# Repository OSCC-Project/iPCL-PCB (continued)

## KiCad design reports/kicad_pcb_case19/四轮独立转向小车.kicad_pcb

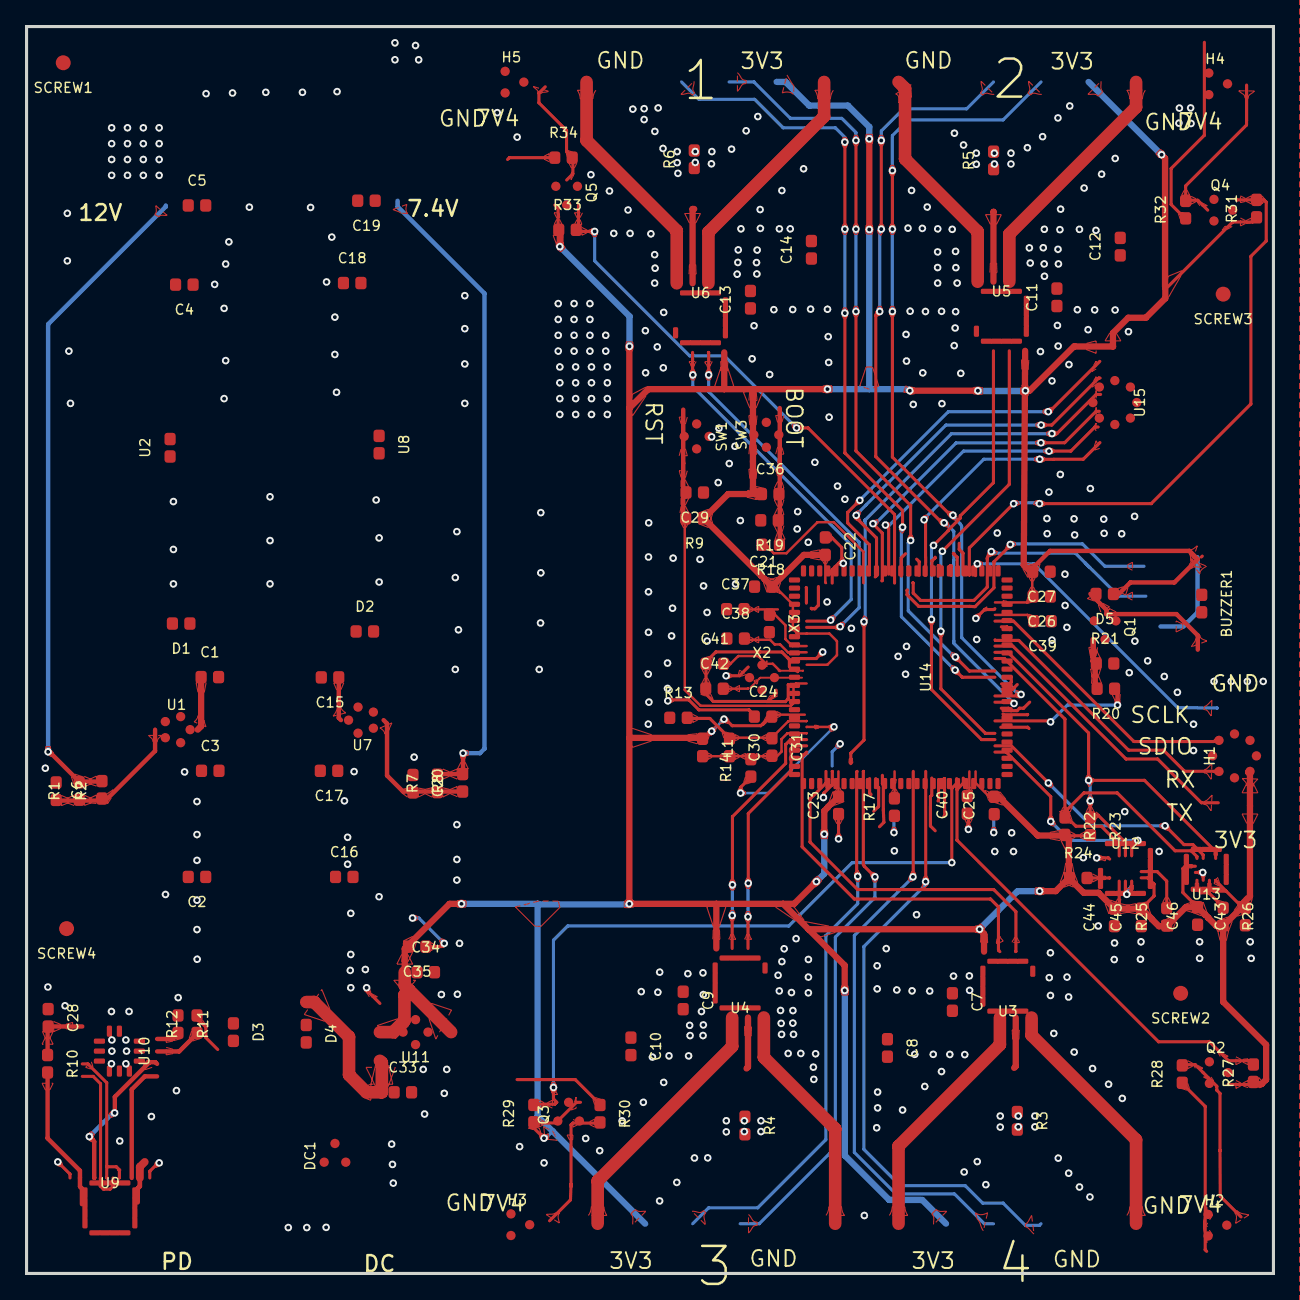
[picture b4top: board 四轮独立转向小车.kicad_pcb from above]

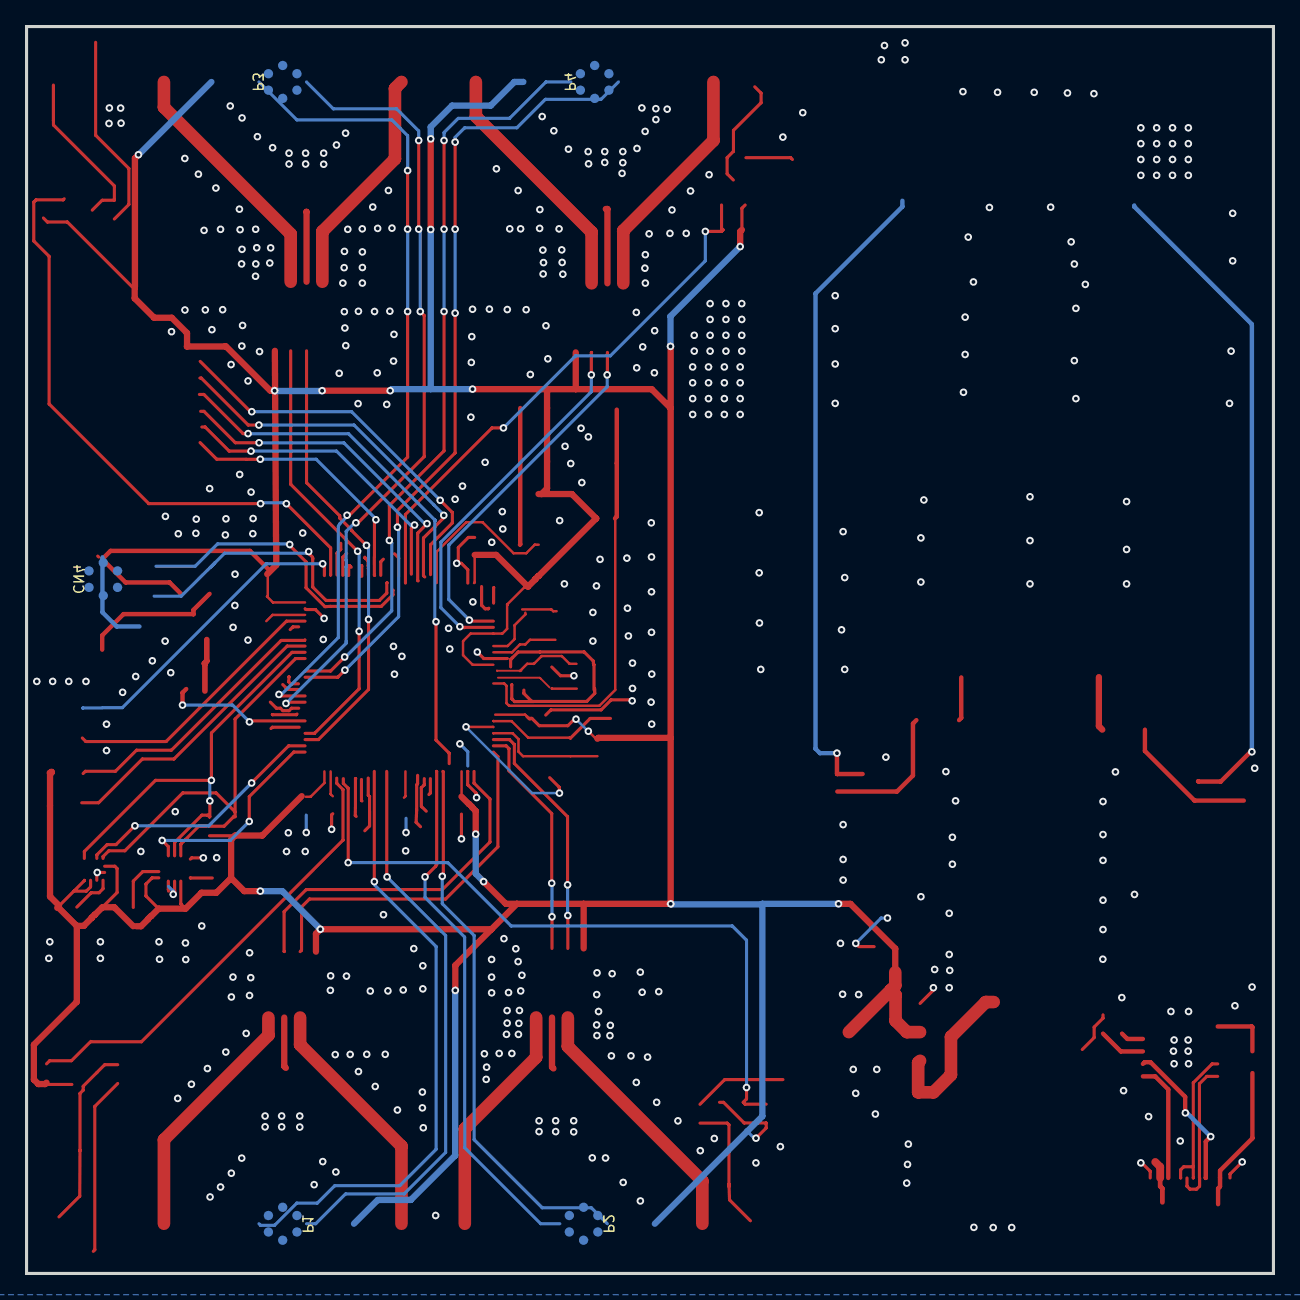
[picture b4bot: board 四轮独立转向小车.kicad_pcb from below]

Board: 4 copper layers, 100.0 x 100.0 mm, 123 parts (5 on the bottom side), 91 nets.

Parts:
BUZZER1: e979cdb000ab4426b6223529a4e12ad8
C1, C3, C4, C6, C7, C9, C11, C13, C15, C17, C18, C20, C21, C22, C23, C24, C25, C26, C27, C28, C29, C30, C31, C35, C36, C37, C38, C41, C42, C43, C44, C45, C46: 741784fa20ad4beab9dd8b8cbce97607
C2, C16: 64fdc954f1a842c2a61e7a3a428ba0e8
C5, C19: aa257ccdfc444fe68fbfe26cfeed8af2
C8, C10, C12, C14: 5d8616532ae7487fa34b3cfaab35ec0e
C33, C34: aff1c91bf3bd4904ada184bcb63bd701
C39, C40: ca2c3d94d51b4dcc8ffcb1d0c67fae6c
CN4: a37b095bfeb148db8b87bdfda393230c
D1, D2, D3, D4: ada4b0e957a340438272a068e350ca08
D5: 7c72a01ebf81492eadadbaccff803c14
DC1: a60ba02c803547268dd5888f05c1003b
H1: 648849d55ce94beca6d893b0b88daeda
H2, H3, H4, H5: abe8049b303d404e805f87de02117873
L1: 5148ca10eaa2479eac7b76f1cbba51f9
P1, P2, P3, P4: 0d6f8f50dd17470faea1144c4daec37b
Q1, Q2, Q3, Q4, Q5: d368db2ef12b40499e45a74d16a73474
R1, R2, R7, R8, R9, R11, R12, R13, R14, R17, R18, R19, R21, R22, R23, R24, R25, R26, R27, R28, R29, R30, R31, R32, R33, R34: 1996b2fb973e40a184d52a2e5e193df3
R3, R4, R5, R6: 24935121d17843519fd4a5b349af625d
R10: 4344cacefc0949e29a8e228f16c4cb32
R20: 446156e8ca504404ab86e8dd60b77f34
SCREW1: e53
SCREW2: e54
SCREW3: e55
SCREW4: e56
SW1, SW3: f78937a3961e46c7aa83ae3777a1ced1
U1, U7: 0156e8566a5e4bc490068a3a1a138cdb
U2, U8: a6e5a65120164f159c520d6f95081e2c
U3, U4, U5, U6: 306ac8a366164cb2a66e359fb6504e2e
U9: df7c89edaee04039b94d8ad6f54aed48
U10: 6103e188eda54d98b9a4d66887e412bf
U11: eb6f0a55a64841b28a24ff6840c76e95
U12: 9212da6725b641f1870fb3cf18556f1c
U13: a1272321b06a4e088013c99c4785c5c8
U14: ac645093d34d4da5947e929ac4406eff
U15: 91d99640c4a348eb8a20141652c3be94
X2: 028e88c81bcf4cf5a4c76024a7a6c317
X3: 518fd2fe129c4e2f80eda365652bfc47

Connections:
7.4V: C18.2, C19.1, C20.2, H2.2, H3.2, H4.2, H5.2, R7.2, R28.1, R30.1, R32.1, R34.1, U8.2
12V: C4.2, C5.1, C6.2, C7.2, C8.1, C9.2, C10.1, C11.2, C12.1, C13.2, C14.1, R1.2, U2.2, U3.5, U4.5, U5.5, U6.5
$1N946: P1.1, U3.8
$1N950: P1.6, U3.6
$1N1291: R3.1, U3.7
$1N2982: C1.1, U1.4
$1N3021: D1.1, U1.3, U2.1
$1N3970: C6.1, R1.1, R2.2, U1.2
$1N4759: P2.6, U4.6
$1N4761: R4.1, U4.7
$1N4762: P2.1, U4.8
$1N5052: P3.6, U5.6
$1N5054: R5.1, U5.7
$1N5055: P3.1, U5.8
$1N5345: P4.6, U6.6
$1N5347: R6.1, U6.7
$1N5348: P4.1, U6.8
$1N5797: C20.1, R7.1, R8.2, U7.2
$1N5800: D2.1, U7.3, U8.1
$1N5801: C15.1, U7.4
$1N15768: H2.3, Q2.3, R28.2
$1N16087: H3.3, Q3.3, R30.2
$1N16294: H4.3, Q4.3, R32.2
$1N16459: H5.3, Q5.3, R34.2
$2N2977: C40.2, U14.49
$2N2980: C39.2, U14.73
$2N2999: R14.1, U14.21
$2N3034: C36.2, R18.1, R19.1, SW3.3, SW3.4
$2N5724: R17.2, U14.37
$2N6021: U9.A6, U9.B6, U10.4
$2N6027: U9.A7, U9.B7, U10.5
$2N6224: R12.1, U10.8
$2N6576: R11.2, U10.9
$2N6889: D4.3, DC1.1
$2N8508: R24.2, U12.4
$2N8534: R25.2, U12.9
$2N8540: R26.1, U13.7
$2N11019: BUZZER1.2, D5.2, Q1.3
$2N11066: Q1.1, R20.2, R21.1
+3V3: BUZZER1.1, C21.2, C22.2, C23.2, C24.2, C25.2, C26.2, C27.2, C34.1, C35.2, C36.1, C43.2, C44.2, C45.2, C46.2, CN4.4, D5.1, H1.1, H1.3, L1.1, P1.5, P2.5, P3.5, P4.5, Q2.1, Q3.1, Q4.1, Q5.1, R9.1, R22.2, R23.2, R24.1, R25.1, R26.2, R27.1, R29.1, R31.1, R33.1, SW3.1, SW3.2, U3.4, U4.4, U5.4, U6.4, U11.2, U11.4, U12.5, U12.8, U13.5, U13.9, U13.10, U14.6, U14.11, U14.19, U14.28, U14.50, U14.75, U14.100, U15.1
AGND: C30.1, C31.1, R13.2, U14.20
B1A: P4.3, U14.63
B1B: P4.4, U14.64
B2A: P3.3, U14.59
B2B: P3.4, U14.60
B3A: P2.3, U14.32
B3B: P2.4, U14.31
B4A: P1.3, U14.42
B4B: P1.4, U14.40
BOOT0: R18.2, U14.94
BUZZ: R20.1, U14.56
CC1: U9.A5, U10.7
CC2: U9.B5, U10.6
CE: U14.93, U15.2
CS1: U12.12, U14.51
CS2: U13.3, U14.52
CSN: U14.92, U15.3
GND: C2.2, C3.1, C4.1, C5.2, C7.1, C8.2, C9.1, C10.2, C11.1, C12.2, C13.1, C14.2, C16.2, C17.1, C18.1, C19.2, C21.1, C22.1, C23.1, C24.1, C25.1, C26.1, C27.1, C28.1, C29.1, C33.2, C34.2, C35.1, C37.1, C38.1, C39.1, C40.1, C41.1, C42.1, C43.1, C44.1, C45.1, C46.1, CN4.1, D1.3, D2.3, DC1.2, DC1.3, H1.5, H1.7, H2.1, H3.1, H4.1, H5.1, P1.2, P2.2, P3.2, P4.2, Q1.2, R2.1, R3.2, R4.2, R5.2, R6.2, R8.1, R11.1, R13.1, R17.1, R19.2, R21.2, SW1.1, SW1.2, U1.1, U3.1, U3.9, U3.e36, U3.e37, U3.e38, U3.e39, U4.1, U4.9, U4.e36, U4.e37, U4.e38, U4.e39, U5.1, U5.9, U5.e36, U5.e37, U5.e38, U5.e39, U6.1, U6.9, U6.e36, U6.e37, U6.e38, U6.e39, U7.1, U9.A1B12, U9.B1A12, U10.11, U11.1, U12.1, U12.6, U12.7, U13.6, U13.8, U14.10, U14.27, U14.74, U14.99, U15.8, X2.2, X2.4
IRQ: U14.84, U15.7
MISO: U14.90, U15.6
MOSI: U14.91, U15.5
NRST: C29.2, R9.2, SW1.3, SW1.4, U14.14
OSC32_IN: C37.2, U14.8, X3.1
OSC32_OUT: C38.2, U14.9, X3.2
OSC_IN: C41.2, U14.12, X2.3
OSC_OUT: C42.2, U14.13, X2.1
PWM1A: U6.3, U14.5
PWM1B: U6.2, U14.4
PWM1C: Q5.2, R33.2, U14.89
PWM2A: U5.3, U14.54
PWM2B: U5.2, U14.53
PWM2C: Q4.2, R31.2, U14.77
PWM3A: U4.3, U14.23
PWM3B: U4.2, U14.24
PWM3C: Q3.2, R29.2, U14.47
PWM4A: U3.3, U14.25
PWM4B: U3.2, U14.26
PWM4C: Q2.2, R27.2, U14.48
SCL: R23.1, U12.13, U13.1, U14.67
SDA: R22.1, U12.14, U13.4, U14.66
SPI-SCLK: U14.30, U15.4
SWCLK: H1.8, U14.76
SWDIO: H1.6, U14.72
USART1_RX: H1.4, U14.69
USART1_TX: H1.2, U14.68
USART2_RX: CN4.2, U14.87
USART2_TX: CN4.3, U14.86
VBUS: D3.3, R10.2, R12.2, U9.A4B9, U9.B4A9
VDD: C28.2, R10.1, U10.1
VDDA: C30.2, C31.2, L1.2, R14.2, U14.22
VIN: C1.2, C2.1, C3.2, C15.2, C16.1, C17.2, C33.1, D3.1, D4.1, U1.5, U7.5, U11.3

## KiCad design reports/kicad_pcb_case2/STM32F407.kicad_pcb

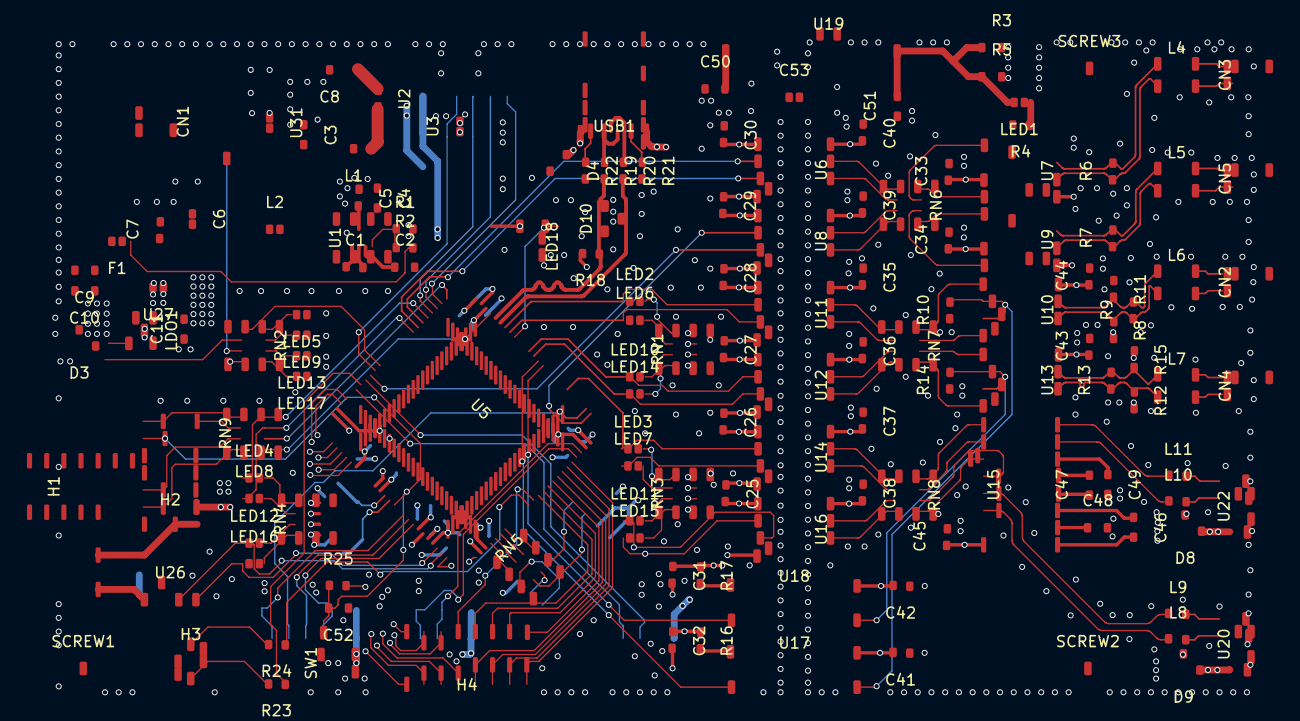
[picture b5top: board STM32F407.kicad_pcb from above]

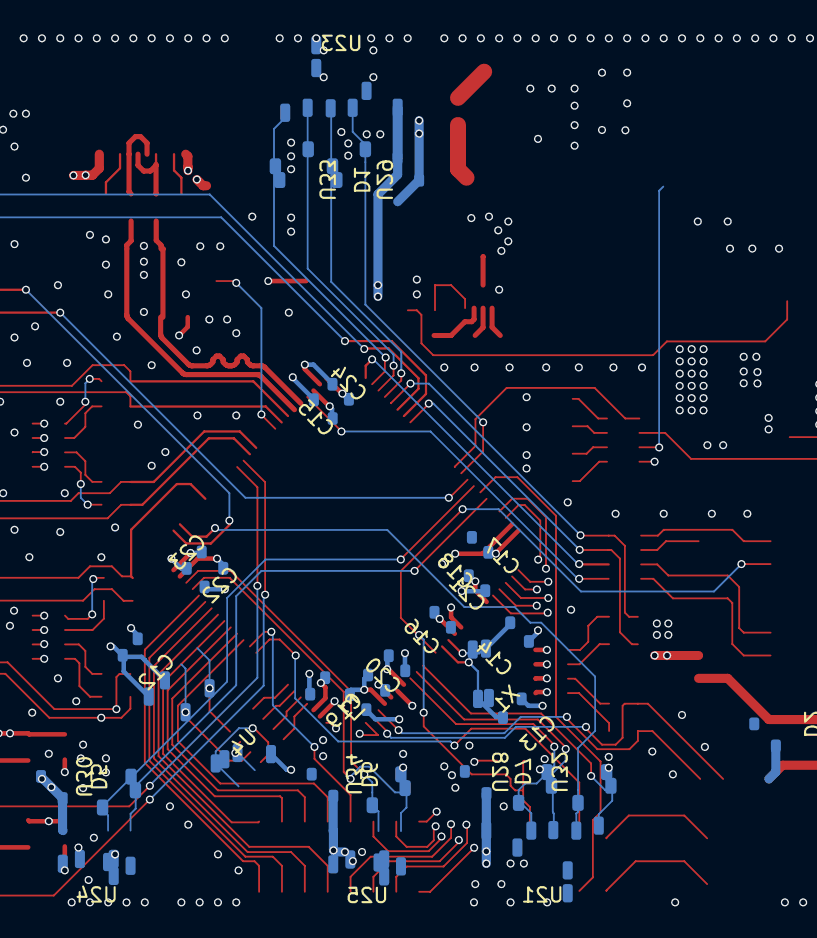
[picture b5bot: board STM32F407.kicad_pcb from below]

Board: 4 copper layers, 177 parts (31 on the bottom side), 166 nets.

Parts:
C1, C5, C7, C12, C15, C16, C17, C18, C19, C20, C21, C22, C25, C26, C27, C28, C29, C30, C31, C32, C33, C34, C35, C36, C37, C38, C39, C40, C41, C42, C43, C44, C45: ebdba0498fe148a6bdaf1849ccadf286
C2, C3, C4, C9, C10, C11, C13, C14, C23, C24, C46, C47, C48, C49, C50, C51, C52: 5c1039116f0d4a48a63c516b3468eedc
C6: 77c1372840904ec4adfa70989b453f34
C8: dac8b4b5750744debf3e22cc36519d09
C53: 722f0fd63bc245dcb5bb6f1de9d44fc4
CN1: a8d795644714433aa9d8ef5899e54b7c
CN2, CN3, CN4, CN5: 8dc8f08645254a7c933896da55491e27
D1, D2, D3, D4, D5, D6, D7, D8, D9: 9031908bb42048fd9eda99e7ea0ed57d
D10: 1d12765dce444169bea8a89c91ace60b
F1: acac5cdf7cf0489f95c57cd956ebba05
H1: c4b2aa7e7e9449449c802d818131b083
H2: c177e7ff2bbf4de4802e46bae8c17754
H3: af64557c0fc140ad852d5d3869016491
H4: 13fd0b7dd5f1483f9419a67b629bdedc
L1: e9d87c9fa1e64efe9140f423ad4aface
L2: 24042ba1875b4ae68b2524adc495f30d
L3, L8, L9, L10, L11: 89a8af1840c5419aa6d14d56da4c8ebb
L4, L5, L6, L7: 2578ce3ca2c0496d87f2ce74849d3ae0
LDO1: 960ec4bb3aa44deea5cfb00bee97f891
LED1: e119
LED2: e121
LED3: e127
LED4: e129
LED5: e114
LED6: e120
LED7: e128
LED8: e137
LED9: e183
LED10: e126
LED11: e180
LED12: e138
LED13: e115
LED14: e122
LED15: e181
LED16: e145
LED17: e182
LED18: 43ac071a49e04e77baa710baadd2d193
R1, R2, R4, R6, R7, R8, R9, R10, R11, R12, R13, R14, R15, R16, R17, R18, R19, R20, R21, R22, R23, R24, R25: 8eb41c1356a64d5a89688063e5a29866
R3, R5: 1b18a010265d471c96efb00eae83c3fd
RN1, RN2, RN3, RN4, RN5, RN6, RN7, RN8, RN9: 2d9df88f5cb64a93977683380616dc51
SCREW1: e123
SCREW2: e124
SCREW3: e125
SW1: efcb0d994e4a4c97aabd31c9830287d5
U1: 15c443d2e1db4dc2b94e34a7db02dd20
U2: 8eb41c1356a64d5a89688063e5a29866
U3: 94e88e65a31343e1b2ef320e804c3fe9
U4: ed3ae879f37841489638cf463064b2e9
U5: 702827d8cd244652a8c957c2584a68a3
U6, U8, U11, U12, U14, U16: 51f0659d1b89481c952678486102db75
U7, U9: 795edbe8080c42678b7c83009ee8dda9
U10, U13: 08b2b6f7ec8347719ef9c282fbdb4a98
U15: f02a3915c41541a1876bc8493e75c0a5
U17, U18: 6089bf52aced4419a38cccb1e1e2119c
U19: 7f6d8a3a13634d468399499959319597
U20, U22, U24, U25: a9433511565944b6b4d3b77f9386d7fd
U21, U23: 48e620de49c44dc5874424a0f0b4b8ec
U26: 6fb28d1a64be4bf99e264b9b66ea87b4
U27: 1bfae8d0649a41a59c4de595a2b109d1
U28, U29, U30, U32, U33, U34: 2d09ce42ff4448d79a78d05c1c820847
U31: 3e6dba7158d148109233be8d25d8f9b1
USB1: 7e44e2b238ab4ac2876cbe0247efab15
X1: 2f487b9613c04c2f98ecb5797db40c7a

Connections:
232_1_RX: L8.2, U20.3
232_1_TX: L9.2, U20.4
232_2_RX: L10.2, U22.3
232_2_TX: L11.2, U22.4
485_1_A: CN2.1, L6.3
485_1_B: CN2.2, L6.4
485_2_A: CN4.1, L7.3
485_2_B: CN4.2, L7.4
$1N123763: C8.1, U2.1
$1N124316: C4.2, C5.2, L1.2, U1.3, U2.2, U3.1
$1N124327: C1.1, L2.1, U1.5
$1N124343: C1.2, U1.6
$1N124356: R1.1, R2.1, U1.8
$1N124450: C2.1, U1.7
$1N125064: LED1.1, R4.1
$1N125152: LED2.2, RN1.5
$1N131581: LED4.2, RN4.5
$1N131583: LED8.2, RN4.6
$1N131585: LED12.2, RN4.7
$1N131593: LED16.2, RN4.8
$1N140993: LED5.2, RN2.8
$1N141105: LED13.2, RN2.6
$1N141109: LED17.2, RN2.5
$1N141153: LED9.2, RN2.7
$1N141345: C6.2, C7.1, F1.1, L2.2, R2.2
$1N145605: LED3.2, RN3.5
$1N145607: LED7.2, RN3.6
$1N145659: LED15.2, RN3.8
$1N145661: LED11.2, RN3.7
$1N145713: LED14.2, RN1.8
$1N145715: LED10.2, RN1.7
$1N145775: LED6.2, RN1.6
$2N590: C23.1, U5.49
$2N591: C24.1, U5.73
$2N663: L3.2, U5.21
$3N1505: H2.7, RN9.6
$3N1506: H2.8, RN9.5
$3N1507: H2.12, RN9.7
$3N1508: H2.13, RN9.8
$3N1509: H3.3, R23.2
$3N1516: H3.4, R24.2
$3N5226: R22.1, USB1.10
$3N5265: R21.1, USB1.4
$3N6048: R19.1, USB1.6, USB1.8
$3N6052: R20.1, USB1.5, USB1.7
$4N2206: L4.1, R6.2, U7.7
$4N6216: RN8.1, U14.7
$4N6221: RN8.3, U16.7
$4N6226: RN8.4, U16.6
$4N6231: RN8.2, U14.6
$4N6248: RN7.2, U11.6
$4N6252: RN7.1, U11.7
$4N6256: RN7.4, U12.6
$4N6260: RN7.3, U12.7
$4N6264: RN6.2, U6.6
$4N6268: RN6.1, U6.7
$4N6272: RN6.4, U8.6
$4N6276: RN6.3, U8.7
$4N8748: RN6.8, U7.4
$4N8754: RN6.7, U7.1
$4N8812: L4.2, R6.1, U7.6
$4N8845: RN6.6, U9.4
$4N8849: RN6.5, U9.1
$4N9061: L5.1, R7.2, U9.7
$4N9079: L5.2, R7.1, U9.6
$4N10322: RN7.7, U10.4
$4N11551: RN7.8, U10.1
$4N11569: RN7.5, U13.4
$4N11573: RN7.6, U13.1
$4N12037: L7.2, R12.1, R13.1, U13.6
$4N12047: L7.1, R13.2, R15.2, U13.7
$4N12057: L6.1, R9.2, R11.2, U10.7
$4N12067: L6.2, R8.1, R9.1, U10.6
$4N28005: C48.1, U15.2
$4N29856: C49.1, U15.6
$4N29863: C46.2, U15.1
$4N29865: C47.1, U15.4
$4N29900: C46.1, U15.3
$4N29905: C47.2, U15.5
$4N29961: RN8.7, U15.10
$4N29965: RN8.8, U15.9
$4N29970: RN8.5, U15.11
$4N29975: RN8.6, U15.12
$4N30026: L8.1, U15.14
$4N30067: L9.1, U15.13
$4N30105: L10.1, U15.7
$4N30146: L11.1, U15.8
$4N30658: R16.2, U17.1
$4N30711: R17.2, U18.1
+5V: C9.1, C10.1, C25.2, C26.2, C27.2, C28.2, C29.2, C30.2, C31.1, C32.1, C50.2, D1.1, D2.1, D3.1, D4.1, D5.1, D6.1, D7.1, F1.2, H1.1, H1.2, H1.3, H1.4, H1.5, H1.6, H1.7, H2.1, LDO1.1, LDO1.3, LED18.1, R16.1, R17.1, RN2.2, U6.1, U8.1, U11.1, U12.1, U14.1, U16.1, U19.1, U21.1, U23.1, U24.1, U25.1, U26.1, USB1.2, USB1.11
+5V_A: C33.1, C34.1, C35.2, C36.2, C37.2, C38.2, C39.2, C40.2, C41.2, C42.2, C43.1, C44.1, C45.1, C51.2, D8.1, D9.1, LED1.2, R3.1, R5.1, R8.2, R12.2, U6.8, U7.3, U7.5, U8.8, U9.3, U9.5, U10.8, U11.8, U12.8, U13.8, U14.8, U15.16, U16.8, U17.4, U18.4, U19.4, U20.1, U22.1
BOOT0: R23.1, U5.94
BOOT1: R24.1, U5.37
CAN_1_H: CN3.2, L4.4
CAN_1_L: CN3.1, L4.3
CAN_1_RX: U5.81, U6.2
CAN_1_TX: U5.82, U6.3
CAN_2_H: CN5.2, L5.4
CAN_2_L: CN5.1, L5.3
CAN_2_RX: U5.51, U8.2
CAN_2_TX: U5.92, U8.3
CS: RN5.1, U4.1
FLASH_CS: RN5.8, U5.29
FLASH_MISO: RN5.6, U5.31
FLASH_MOSI: RN5.5, U5.32
FLASH_SCK: RN5.7, U5.30
GND: C2.2, C3.1, C4.1, C5.1, C6.1, C7.2, C8.2, C9.2, C10.2, C11.1, C12.2, C13.2, C14.2, C15.1, C16.1, C17.1, C18.1, C19.1, C20.1, C21.1, C22.1, C23.2, C24.2, C25.1, C26.1, C27.1, C28.1, C29.1, C30.1, C31.2, C32.2, C50.1, C52.1, C53.1, CN1.1, CN1.3, CN1.4, D1.2, D2.2, D3.2, D4.2, D5.2, D6.2, D7.2, D10.3, H1.8, H1.9, H1.10, H1.11, H1.12, H1.13, H1.14, H2.3, H2.4, H3.5, H3.6, LDO1.2, LED5.1, LED9.1, LED13.1, LED17.1, LED18.3, R1.2, R21.2, R22.2, SW1.3, SW1.4, U1.4, U3.2, U5.10, U5.20, U5.27, U5.74, U5.99, U6.4, U8.4, U11.4, U12.4, U14.4, U16.4, U19.2, U21.2, U21.7, U21.8, U23.2, U23.7, U23.8, U24.2, U24.5, U24.6, U25.2, U25.5, U25.6, U26.2, U27.2, U28.3, U29.3, U30.3, U31.1, U32.3, U33.3, U34.3, USB1.1, USB1.12, USB1.13, USB1.14, X1.2, X1.4
I2C1_SCL: U5.95, U24.4, U30.2
I2C1_SDA: U5.93, U24.3, U30.1
I2C2_SCL: U5.47, U25.4, U34.2
I2C2_SDA: U5.48, U25.3, U34.1
MISO: RN5.3, U4.2
MOSI: RN5.4, U4.5
NRST: C52.2, H2.9, R25.1, SW1.2, U5.14
OSC_IN: C14.1, U5.12, X1.3
OSC_OUT: C13.1, U5.13, X1.1
PE0: H4.13, U5.97
PE1: H4.15, U5.98
PE2: H4.11, U5.1
PE3: H4.10, U5.2
PE4: H4.12, U5.3
PE5: H4.14, U5.4
PE6: H4.16, U5.5
PE7: H4.9, U5.38
PE8: H4.7, U5.39
PE9: H4.5, U5.40
PE10: H4.3, U5.41
PE11: H4.1, U5.42
PE12: H4.8, U5.43
PE13: H4.6, U5.44
PE14: H4.4, U5.45
PE15: H4.2, U5.46
PGND: C33.2, C34.2, C35.1, C36.1, C37.1, C38.1, C39.1, C40.1, C41.1, C42.1, C43.2, C44.2, C45.2, C48.2, C49.2, C51.1, C53.2, CN2.3, CN2.4, CN3.3, CN3.4, CN4.3, CN4.4, CN5.3, CN5.4, D8.2, D9.2, R3.2, R4.2, R5.2, R10.1, R11.1, R14.1, R15.1, U6.5, U7.2, U7.8, U8.5, U9.2, U9.8, U10.5, U11.5, U12.5, U13.5, U14.5, U15.15, U16.5, U19.3, U20.2, U20.5, U20.6, U22.2, U22.5, U22.6
R485_1_EN: U5.62, U17.2
R485_1_R/D: R10.2, U10.2, U10.3, U17.3
R485_2_EN: U5.61, U18.2
R485_2_R/D: R14.2, U13.2, U13.3, U18.3
SCK: RN5.2, U4.6
SPI2_CS: U5.16, U21.6, U32.2
SPI2_MISO: U5.17, U21.4, U28.2
SPI2_MOSI: U5.18, U21.3, U28.1
SPI2_SCK: U5.52, U21.5, U32.1
SPI3_CS: U5.77, U23.6, U33.2
SPI3_MISO: U5.79, U23.4, U29.2
SPI3_MOSI: U5.91, U23.3, U29.1
SPI3_SCK: U5.78, U23.5, U33.1
SWCLK: RN9.2, U5.76
SWDIO: RN9.1, U5.72
TEST_LED: RN2.1, U5.90
U1_R485_RX: LED2.1, U5.69, U11.2
U1_R485_TX: LED6.1, U5.68, U11.3
U2_R232_RX: LED15.1, U5.26, U16.2
U2_R232_TX: LED11.1, U5.25, U16.3
U3_R232_RX: LED3.1, U5.56, U14.2
U3_R232_TX: LED7.1, U5.55, U14.3
U4_RF_RX: LED12.1, U5.24, U26.3
U4_RF_TX: LED16.1, U5.23, U26.4
U5_TEST_RX: LED8.1, RN9.3, U5.83
U5_TEST_TX: LED4.1, RN9.4, U5.80
U6_R485_RX: LED10.1, U5.64, U12.2
U6_R485_TX: LED14.1, U5.63, U12.3
USB_DM: D10.1, R20.2, U5.70
USB_DP: D10.2, R18.1, R19.2, U5.71
VBAT: C3.2, CN1.2, L1.1, RN2.3, U31.2
VCC: C11.2, C12.1, C15.2, C16.2, C17.2, C18.2, C19.2, C20.2, C21.2, C22.2, H2.2, H3.1, H3.2, L3.1, LDO1.5, R18.2, R25.2, RN1.1, RN1.2, RN1.3, RN1.4, RN2.4, RN3.1, RN3.2, RN3.3, RN3.4, RN4.1, RN4.2, RN4.3, RN4.4, U4.3, U4.7, U4.8, U5.6, U5.11, U5.19, U5.22, U5.28, U5.50, U5.75, U5.100, U27.1
WS2812: LED18.4, U5.67

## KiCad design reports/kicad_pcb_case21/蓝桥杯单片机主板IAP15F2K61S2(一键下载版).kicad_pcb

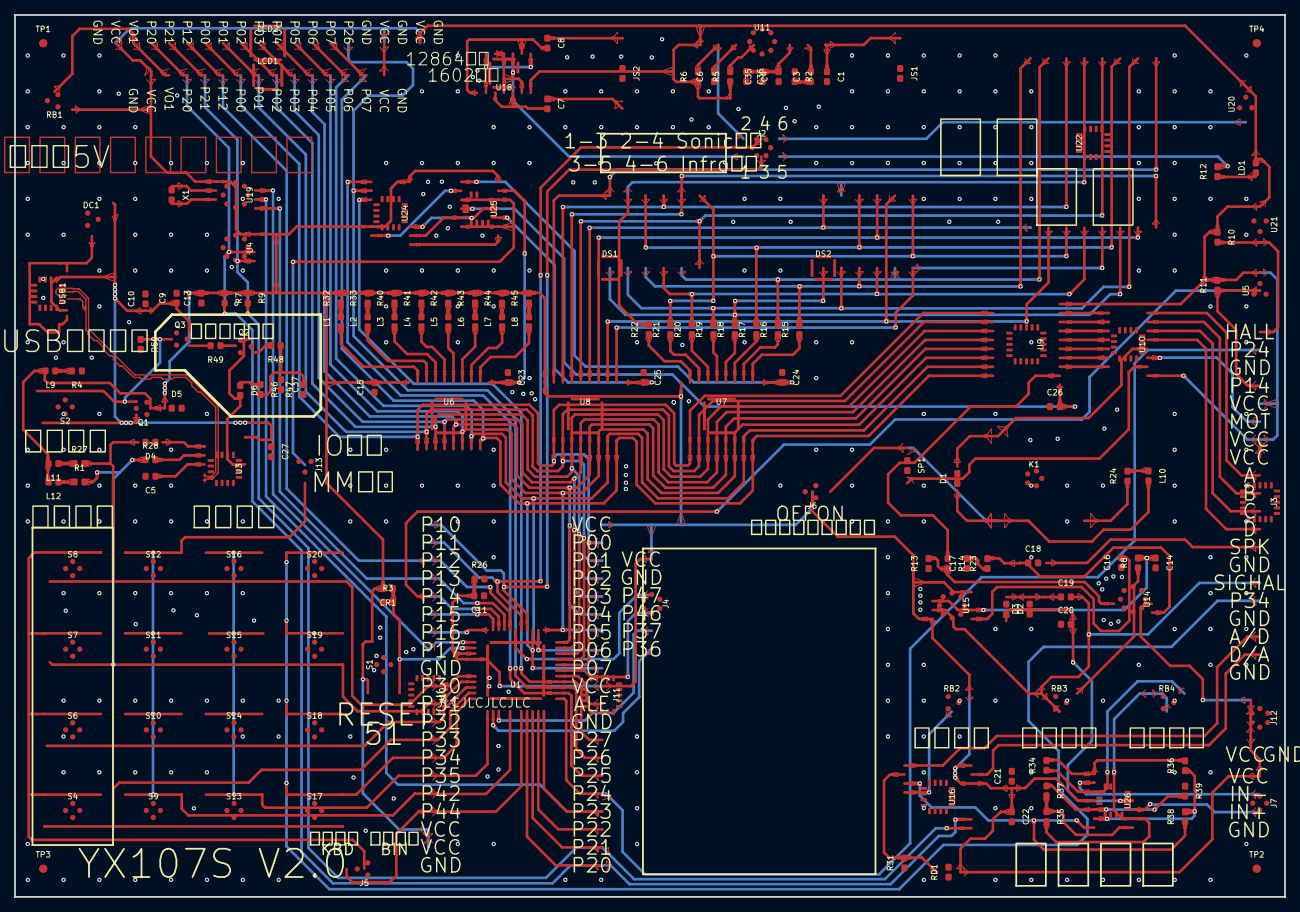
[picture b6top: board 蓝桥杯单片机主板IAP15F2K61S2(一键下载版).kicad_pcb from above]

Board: 4 copper layers, 180.0 x 125.0 mm, 167 parts (0 on the bottom side), 169 nets.

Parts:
C1, C3, C4, C5, C6, C7, C8, C9, C11, C13, C14, C15, C16, C17, C22, C23, C24, C25, C26, C35, C36: 67112287d2d841138a63fa2f631ec745
C10, C21, C27, C37: 8ecdcd2dd93a4a1aa3b683c34e9b51bd
C18: 250162ae301a4f9c8ce6380c858be1a2
C19, C20: cac0db1b05df413eb2f95180b1807fe2
CR1: 67112287d2d841138a63fa2f631ec745
D1, D2, D3, D4, D5: a2a0d38c0278464888e498b54d42c51a
D6: ceb02d1e43f7479da29f8f3361369faa
DC1: 9bb7e9c4d11141c69c37d7f296efa099_e76
DS1, DS2: 0f4c41736a254c37994dc45fe2084054
J2, J12: 5726d0255834435aaecaaea19e66b6eb
J3, J10, J11: 3de81db1f2774423be2bab1b690b3233
J4: 9bb7e9c4d11141c69c37d7f296efa099_e70
J5, J6, J13: 6e0d14acf0a44e28ad5cf3190cda4e79
J7: 69489f7a91804813a74497b6d9622d75
JS1, JS2: 135c43c305c843ba92a00f2ebe928e15
K1: 7f2fabe4f9114650901f66b24200dfa6
L1, L2, L3, L4, L5, L6, L7, L8, L9, L10, L11, L12: 17468d434007488e9983de3bb2c82029
LCD1: 81a8a83525b342d88cfb02cf0e821dd7
LCD2: 3de81db1f2774423be2bab1b690b3233
LD1: d29f5bd2aed24487ad12fc9b40131697
Q1: 0c5518d332ec4aada29a8d429bb7030e
Q2: e27
Q3: e96
R1, R2, R3, R4, R5, R6, R7, R8, R9, R10, R11, R12, R13, R14, R15, R16, R17, R18, R19, R20, R21, R22, R23, R24, R26, R27, R28, R31, R32, R33, R34, R35, R36, R37, R38, R39, R40, R41, R42, R43, R44, R45, R46, R47, R48, R49, R50: f6c6c77cf312463ca31a7274132b1319
RB1, RB2, RB3, RB4: 8f4631625b164f779cc032a2dec21355
RD1: f37982cbe8f1436c99f6961d78790b54
S1, S2, S4, S6, S7, S8, S9, S10, S11, S12, S13, S14, S15, S16, S17, S18, S19, S20: 63428a2f046344f4b5b69b84a01701ed
SP1: a2f27cf5069b456d9d3bb516ab3f4cdd
TP1: e1111
TP2: e1112
TP3: e1113
TP4: e1114
U1: 9a1bc23669d14af083f2d402f6e7dfdb
U3: e5078b6359cd473a981263d1673a8c97
U4, U14: 1da5b987d6384a2e8418f4ef1a4bb25b
U5: 9bb7e9c4d11141c69c37d7f296efa099_e159
U6, U7, U8, U9: f0259679606740a487d96540d571f821
U10, U24: 714cf57d8be0478e85081397330cccac
U11: 4739b0249a224a73b0eebe1e27752588
U15: bb8f4ad1b4b147308fd5aba69e3e1860
U16: d18e5e4e8c6c4dc9a5d58b351d5fb804
U18: 3db808bd86114eafbf0638d27fac0128
U19: 527203e2beca4eef839ace3cb4f0e03c
U20: 87f8bdce36f8484897564a97db86b257
U21: 9bb7e9c4d11141c69c37d7f296efa099_e46
U22: 9bb7e9c4d11141c69c37d7f296efa099_e53
U25: 55504cd69bec4a1a8830e6febb516af0
U26: bb4262cf69134720bce52561960afb51
USB1: a4d8271706d14f2e8dd54a7a11dcef38
X1: 1c301c57f75f4976bda87158dbc0e1df

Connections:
$1N2230: L4.1, U6.16
$1N2233: L3.1, U6.17
$1N2236: L2.1, U6.18
$1N2239: L1.1, U6.19
$1N2242: L4.2, R41.1
$1N2245: L3.2, R40.1
$1N2248: L2.2, R33.1
$1N2251: L1.2, R32.1
$1N2416: L8.1, U6.12
$1N2418: L7.1, U6.13
$1N2420: L6.1, U6.14
$1N2422: L5.1, U6.15
$1N2424: L8.2, R45.1
$1N2426: L7.2, R44.1
$1N2428: L6.2, R43.1
$1N2430: L5.2, R42.1
$1N5344: U9.13, U10.7
$1N5345: U9.14, U10.6
$1N5347: U9.15, U10.5
$1N5349: U9.16, U10.4
$1N5351: U9.17, U10.3
$1N5353: U9.18, U10.2
$1N5355: U9.19, U10.1
$1N6699: C18.1, R23.2, U14.5
$1N6846: C17.2, R23.1
$1N7044: R13.2, R14.2, U14.3
$1N8508: C5.1, U3.4
$1N8571: D4.1, U3.2
$1N8648: R28.2, U3.3
$1N9521: L9.1, R4.2
$1N9746: R22.1, U7.19
$1N9748: R21.1, U7.18
$1N9750: R20.1, U7.17
$1N9752: R19.1, U7.16
$1N9754: R18.1, U7.15
$1N9756: R17.1, U7.14
$1N9758: R16.1, U7.13
$1N9760: R15.1, U7.12
$1N9888: L10.1, R24.2
$1N10701: C14.1, R8.2, U15.2, U15.6
$1N10759: C16.2, U15.5
$1N10864: R8.1, RB3.3
$1N11053: C19.1, D2.1, D3.2
$1N21686: J5.2, S4.1, S4.2, S6.1, S6.2, S7.1, S7.2, S8.1, S8.2
$1N21985: U18.1, U18.6, U18.9
$1N22024: U18.4, U18.5, U18.11, U18.13
$1N22091: C7.2, U18.10, U18.12
$1N22097: C8.2, U18.2, U18.8
$1N22290: C7.1, JS2.2
$1N22294: C8.1, JS2.1
$1N22418: C1.1, JS1.1, U11.1
$1N22570: C3.2, U11.2
$1N22573: C3.1, R2.2
$1N26338: R5.2, U11.5
$1N26390: C6.2, U11.6
$1N26677: C4.2, C35.2, C36.1, U11.3
$1N27219: LD1.1, R12.1
$1N27573: U19.2, X1.1
$1N27577: U19.3, X1.2
$1N28313: R34.2, R36.2, U26.1
$1N28323: R34.1, RB4.3, U26.3
$1N28392: R35.2, RB4.1, RB4.2, U26.9
$1N28443: R35.1, R37.2, U26.8
$1N28533: R37.1, R39.2, U26.5
$1N28538: R36.1, R38.2, U26.6
$1N33464: L12.1, R1.1
$1N33546: L11.1, R27.1
$1N74796: D6.1, R46.1
$1N74943: C37.1, R46.2, R47.2, R48.1
$1N74991: Q2.1, R48.2
$1N75122: Q2.3, R49.1
$1N75151: Q3.1, R49.2
$1N75232: Q1.1, Q3.3, R50.1, S2.3, S2.4
$1N75271: D6.2, Q2.2, U3.13
A1: DS1.11, DS2.11, R22.2, U22.13
AIN0: J3.18, U16.1
AIN1: R31.2, RD1.1, U16.2
AIN2: R38.1, U16.3, U26.7
AIN3: RB2.2, U16.4
ALE: J11.11, U1.38
B1: DS1.7, DS2.7, R21.2, U22.3
C1: DS1.4, DS2.4, R20.2, U22.4
COM1: DS1.12, U8.19, U22.9
COM2: DS1.9, U8.18, U22.14
COM3: DS1.8, U8.17, U22.8
COM4: DS1.6, U8.16, U22.12
COM5: DS2.12, U8.15, U22.1
COM6: DS2.9, U8.14, U22.7
COM7: DS2.8, U8.13, U22.2
COM8: DS2.6, U8.12, U22.5
D1: DS1.2, DS2.2, R19.2, U22.10
D+: U3.5, USB1.A6, USB1.B6
D-: U3.6, USB1.A7, USB1.B7
DP1: DS1.3, DS2.3, R15.2, U22.16
E1: DS1.1, DS2.1, R18.2, U22.6
F1: DS1.10, DS2.10, R17.2, U22.11
G1: DS1.5, DS2.5, R16.2, U22.15
GND: C1.2, C4.1, C5.2, C6.1, C9.2, C10.2, C11.1, C13.1, C14.2, C15.1, C16.1, C17.1, C20.1, C21.2, C22.2, C23.1, C24.1, C25.1, C26.1, C27.2, C35.1, C36.2, C37.2, D3.1, D5.2, DC1.2, J3.3, J3.14, J3.17, J3.20, J4.2, J5.1, J7.4, J10.9, J10.20, J11.12, J12.2, J12.4, J12.6, J13.1, JS1.2, K1.5, LCD1.1, LCD1.16, LCD2.1, LCD2.16, LCD2.18, LCD2.20, R2.1, R3.1, R4.1, R13.1, R26.2, R31.1, R39.1, R47.1, R50.2, RB1.3, RB2.1, U1.16, U3.1, U4.1, U4.2, U4.3, U4.4, U4.7, U5.1, U6.1, U6.10, U7.1, U7.10, U8.1, U8.10, U9.1, U9.10, U10.8, U11.4, U14.2, U14.4, U15.1, U16.5, U16.6, U16.7, U16.8, U16.12, U16.13, U18.7, U19.4, U20.2, U21.2, U24.4, U24.5, U24.8, U25.7
GNDUSB: DC1.3, USB1.0, USB1.A1B12, USB1.B1A12
IN+: J7.3, U26.10
IN-: J7.2, U26.2
M2: K1.2, R24.1
NET_SIG: C19.2, J3.15, RB3.1, RB3.2, U15.3
N_A1: J2.1, U18.3
N_A2: J2.5, R12.2
N_B1: J2.2, R6.2, U11.7
N_B2: J2.6, U20.1
N_BUZZ: SP1.2, U10.10
N_HALL: J3.1, R10.2, U21.3
N_MOTOR: J3.6, U10.11
N_RELAY: D1.2, K1.4, U10.12
N_SPK: R14.1, U9.12
OUT: J3.19, U16.15
P00: J11.2, LCD1.7, LCD2.7, U1.40, U6.2, U7.2, U8.2, U9.2
P01: J11.3, LCD1.8, LCD2.8, U1.41, U6.3, U7.3, U8.3, U9.3
P02: J11.4, LCD1.9, LCD2.9, U1.42, U6.4, U7.4, U8.4, U9.4
P03: J11.5, LCD1.10, LCD2.10, U1.43, U6.5, U7.5, U8.5, U9.5
P04: J11.6, LCD1.11, LCD2.11, U1.44, U6.6, U7.6, U8.6, U9.6
P05: J11.7, LCD1.12, LCD2.12, U1.1, U6.7, U7.7, U8.7, U9.7
P06: J11.8, LCD1.13, LCD2.13, U1.2, U6.8, U7.8, U8.8, U9.8
P07: J11.9, LCD1.14, LCD2.14, U1.3, U6.9, U7.9, U8.9, U9.9
P10: J2.3, J10.1, U1.4
P11: J2.4, J10.2, U1.5
P12: J10.3, LCD1.6, LCD2.6, U1.7
P13: J10.4, U1.8, U19.5
P14: J3.4, J10.5, R11.1, U1.9, U5.2
P15/MOSI: J10.6, U1.10
P16/MISO: J10.7, U1.11
P17/SCK: J10.8, U1.12, U19.7
P20/SCL: J11.20, LCD1.4, LCD2.4, R7.2, U1.30, U4.6, U16.10
P21/SDA: J11.19, LCD1.5, LCD2.5, R9.2, U1.31, U4.5, U16.9
P22: J11.18, U1.32
P23: J11.17, U1.33, U19.6
P24: J3.2, J11.16, U1.34
P25: J11.15, U1.35, U24.1
P26: J11.14, LCD2.15, U1.36, U24.2
P27: J11.13, U1.37, U24.3
P30/TXD: D4.2, J10.10, R27.2, S8.3, S8.4, S12.3, S12.4, S16.3, S16.4, S20.3, S20.4, U1.18
P31/RXD: J10.11, R1.2, R28.1, S7.3, S7.4, S11.3, S11.4, S15.3, S15.4, S19.3, S19.4, U1.19
P32: J10.12, S6.3, S6.4, S10.3, S10.4, S14.3, S14.4, S18.3, S18.4, U1.20
P33: J10.13, S4.3, S4.4, S9.3, S9.4, S13.3, S13.4, S17.3, S17.4, U1.21
P34: J3.16, J10.14, S17.1, S17.2, S18.1, S18.2, S19.1, S19.2, S20.1, S20.2, U1.22
P35: J10.15, S13.1, S13.2, S14.1, S14.2, S15.1, S15.2, S16.1, S16.2, U1.23
P36: J4.6, U1.24
P37: J4.5, U1.25
P42/WR: J10.16, J13.3, S9.1, S9.2, S10.1, S10.2, S11.1, S11.2, S12.1, S12.2, U1.27
P44/RD: J5.3, J10.17, U1.29
P46: J4.4, U1.39
P47: J4.3, U1.6
RST: CR1.1, R3.2, S1.3, S1.4, U1.13
SPK: C18.2, J3.13
STEPA: J3.9, U10.16
STEPB: J3.10, U10.15
STEPC: J3.11, U10.14
STEPD: J3.12, U10.13
VB: D1.1, J6.1, K1.1, L10.2, SP1.1
VCC: C11.2, C13.2, C15.2, C21.1, C22.1, CR1.2, D5.1, J3.5, J3.7, J3.8, J4.1, J6.2, J7.1, J10.18, J10.19, J11.1, J11.10, J12.1, J12.3, J12.5, L9.2, L11.2, L12.2, LCD1.2, LCD1.15, LCD2.2, LCD2.17, LCD2.19, LD1.2, Q1.3, R5.1, R6.1, R7.1, R9.1, R10.1, R11.2, R26.1, R32.2, R33.2, R40.2, R41.2, R42.2, R43.2, R44.2, R45.2, RB1.1, RB2.3, RD1.2, S1.1, S1.2, U1.14, U1.15, U4.8, U5.3, U6.20, U7.20, U8.20, U9.20, U10.9, U11.8, U14.6, U15.4, U15.8, U16.14, U16.16, U18.14, U19.1, U20.3, U21.1, U24.6, U24.16, U25.14, U26.4
VCCA: C9.1, C10.1, C27.1, DC1.1, Q1.2, Q3.2, S2.1, S2.2, U3.16, USB1.A4B9, USB1.B4A9
VEE: C20.2, D2.2, U26.11
VO1: LCD1.3, LCD2.3, RB1.2
WR: J13.2, U25.3, U25.6, U25.9, U25.12
Y4: U24.11, U25.11
Y4C: C23.2, U6.11, U25.13
Y5: U24.10, U25.5
Y5C: C26.2, U9.11, U25.4
Y6: U24.9, U25.8
Y6C: C25.2, U8.11, U25.10
Y7: U24.7, U25.2
Y7C: C24.2, U7.11, U25.1
